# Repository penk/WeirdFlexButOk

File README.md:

## WeirdFlexButOk 

A hot-swappable unibody ergo split keyboard.

This is inspired by Joe Scotto's handwired [ScottoErgo](https://scottokeebs.com/blogs/keyboards/scottoergo-handwired-keyboard) but opts for Choc spacing and hot-swap sockets, plus a super-bendy 0.8mm PCB with kerf bending cuts. It flexes to follow the case’s contour, providing a 15° tilt and 10° tent from one FR4 PCB. 

## Bill of Materials (BOM)

Quantity | Item 
--- | --- 
1 | RP2040-Zero & Pin headers 
1 | WeirdFlexButOk PCB 
1 | WeirdFlexButOk case & plate
36 | Kailh Choc V1 switches  
36 | Kailh Choc V1 Hot-swap sockets 
36 | 1N4148 diodes (SMD)
2 | WS2812B LEDs (optional, for underglow)
8 | M2x4 heat-set thread inserts
6 | M2x8 standoffs
14 | M2x4 screws 

## Production Files

To place an order for the WeirdFlexButOk PCB:

- Use the Gerber files in the [production/](production/) folder. 
- Optionally, you can utilize the [BOM](production/BOM.csv) and [CPL](production/CPL.csv) files with a PCBA service. All components (except RP2040-Zero) are soldered to the bottom side of the board.

Make sure to select the following specs so the PCB can flex:

- Base Material: `FR4`
- PCB Thickness: `0.8mm` 

The complete PCB design project is in the [kicad/](kicad/) folder. 

## 3D Printable Files 

3D print the case with the provided [STL files](case/). 

|  |  |
|---|---|

There will be a lot of support materials, and the tolerance needs to be tuned right for the switches (14.2x14.2mm) to fit.

I find the following parameters work best for my print:

- Top/Bottom Speed: 30 mm/s 
- Support Structure: Tree
- Fan Speed Override: True
- Support Skin Fan Speed: 100%

## Firmware 

Precompiled VIA-enabled firmware: 

- Flash [penk_weirdflexbutok36_via.uf2](firmware/penk_weirdflexbutok36_via.uf2) to the RP2040-Zero.
- Load the [via.json](firmware/QMK/keyboards/penk/weirdflexbutok36/via.json) file in `Design` tab for [VIA](https://usevia.app) configuration.

## Keycaps

The keycap featured in this image is designed based on the Shiratama profile by [@taneyats](https://twitter.com/taneyats). The original design can be found [here](https://www.taneyats.com/entry/shiratama-profile), and is licensed for non-commercial use under [CC BY-NC 4.0](https://creativecommons.org/licenses/by-nc/4.0).

### Attribution
- **Author:** [@taneyats](https://twitter.com/taneyats)
- **Source:** [Shiratama keycaps](https://taneyats.booth.pm/items/4020198)
- **License:** [Creative Commons Attribution-NonCommercial 4.0 International](https://creativecommons.org/licenses/by-nc/4.0/)

### Derivative Work
The STL file has been modified for Choc spacing and is available here: [Shiratama-choc-1U-set.stl](keycap/Shiratama-choc-1U-set.stl) (Modification by [@penk](https://github.com/penk)).

This adaptation is intended for personal use only.

## Copyright and License
Copyright (c) 2024 Penk Chen. All rights reserved.

All files, except those specifically mentioned as licensed under Creative Commons, are licensed under the MIT license. For more information, see the [LICENSE](LICENSE).

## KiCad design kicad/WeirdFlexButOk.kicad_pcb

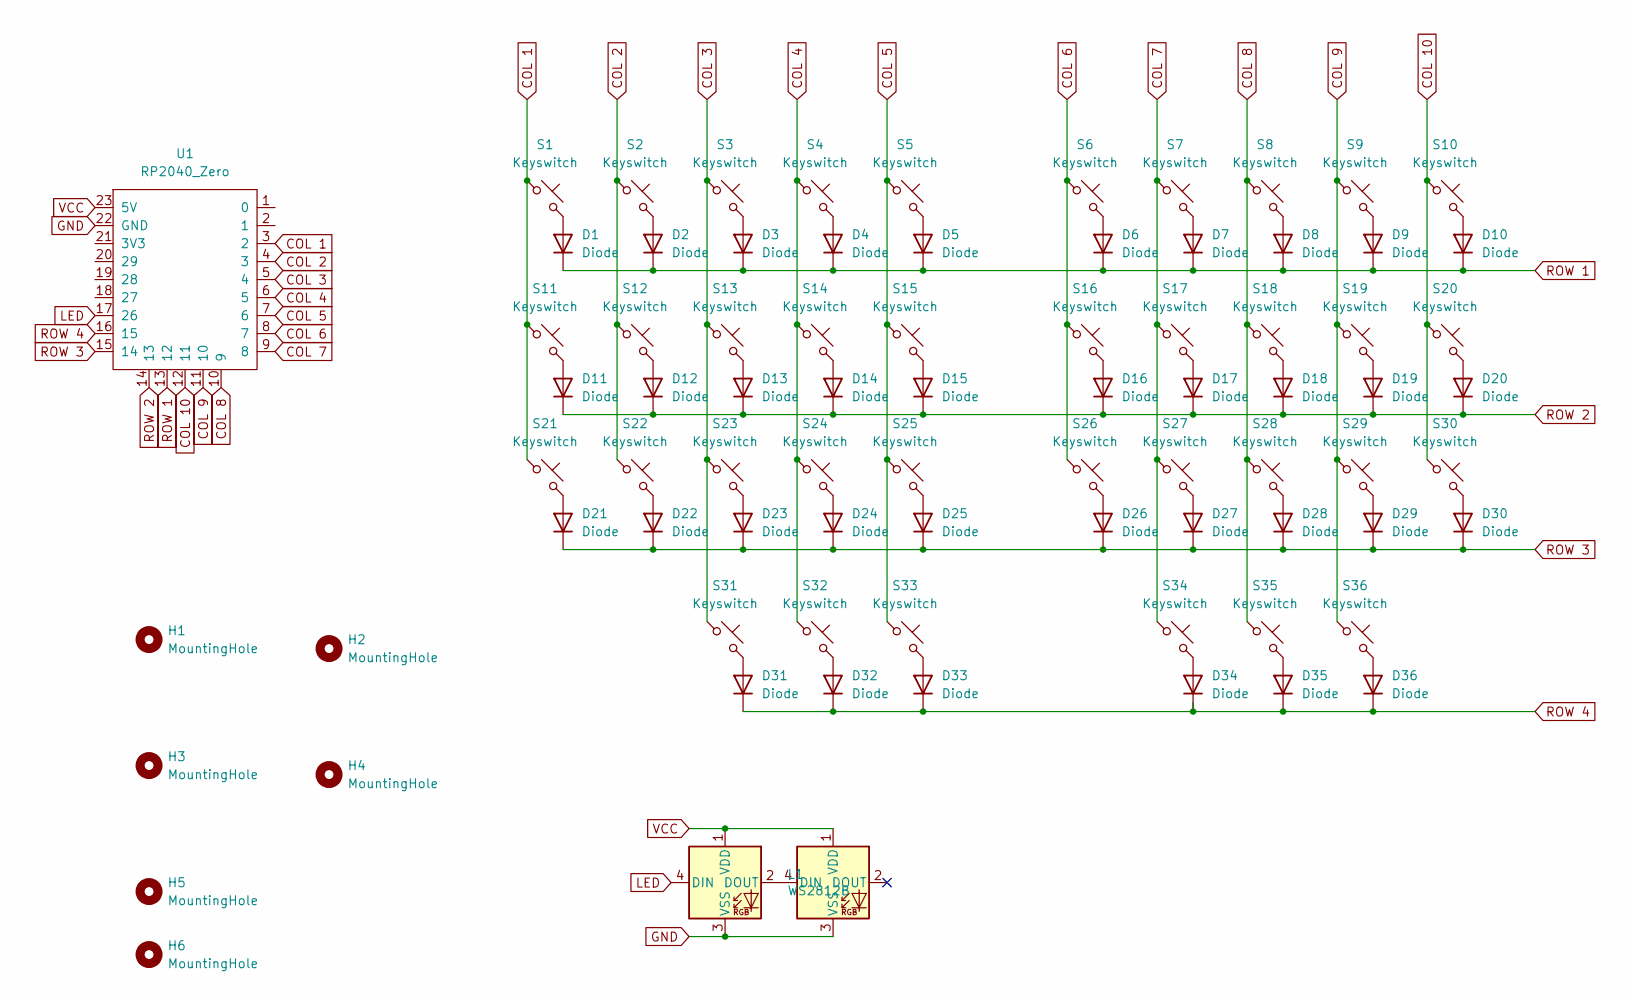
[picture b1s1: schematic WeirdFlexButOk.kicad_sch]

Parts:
D1, D2, D3, D4, D5, D6, D7, D8, D9, D10, D11, D12, D13, D14, D15, D16, D17, D18, D19, D20, D21, D22, D23, D24, D25, D26, D27, D28, D29, D30, D31, D32, D33, D34, D35, D36: Diode; Diode_SOD-123
H1, H2, H3, H4, H5, H6: MountingHole; MountingHole_2.2mm_M2
L1, L2: WS2812B; LED_WS2812B_PLCC4_5.0x5.0mm_P3.2mm
S1, S2, S3, S4, S5, S6, S7, S8, S9, S10, S11, S12, S13, S14, S15, S16, S17, S18, S19, S20, S21, S22, S23, S24, S25, S26, S27, S28, S29, S30, S31, S32, S33, S34, S35, S36: Keyswitch; SW_choc_v1_HS_1u
U1: RP2040_Zero

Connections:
COL 1: S1.1, S11.1, S21.1, U1.3 (2)
COL 2: S2.1, S12.1, S22.1, U1.4 (3)
COL 3: S3.1, S13.1, S23.1, S31.1, U1.5 (4)
COL 4: S4.1, S14.1, S24.1, S32.1, U1.6 (5)
COL 5: S5.1, S15.1, S25.1, S33.1, U1.7 (6)
COL 6: S6.1, S16.1, S26.1, U1.8 (7)
COL 7: S7.1, S17.1, S27.1, S34.1, U1.9 (8)
COL 8: S8.1, S18.1, S28.1, S35.1, U1.10 (9)
COL 9: S9.1, S19.1, S29.1, S36.1, U1.11 (10)
COL 10: S10.1, S20.1, S30.1, U1.12 (11)
GND: L1.3 (VSS), L2.3 (VSS), U1.22 (GND)
LED: L1.4 (DIN), U1.17 (26)
unnamed: D1.2 (A), S1.2
unnamed: D2.2 (A), S2.2
unnamed: D3.2 (A), S3.2
unnamed: D4.2 (A), S4.2
unnamed: D5.2 (A), S5.2
unnamed: D6.2 (A), S6.2
unnamed: D7.2 (A), S7.2
unnamed: D8.2 (A), S8.2
unnamed: D9.2 (A), S9.2
unnamed: D10.2 (A), S10.2
unnamed: D11.2 (A), S11.2
unnamed: D12.2 (A), S12.2
unnamed: D13.2 (A), S13.2
unnamed: D14.2 (A), S14.2
unnamed: D15.2 (A), S15.2
unnamed: D16.2 (A), S16.2
unnamed: D17.2 (A), S17.2
unnamed: D18.2 (A), S18.2
unnamed: D19.2 (A), S19.2
unnamed: D20.2 (A), S20.2
unnamed: D21.2 (A), S21.2
unnamed: D22.2 (A), S22.2
unnamed: D23.2 (A), S23.2
unnamed: D24.2 (A), S24.2
unnamed: D25.2 (A), S25.2
unnamed: D26.2 (A), S26.2
unnamed: D27.2 (A), S27.2
unnamed: D28.2 (A), S28.2
unnamed: D29.2 (A), S29.2
unnamed: D30.2 (A), S30.2
unnamed: D31.2 (A), S31.2
unnamed: D32.2 (A), S32.2
unnamed: D33.2 (A), S33.2
unnamed: D34.2 (A), S34.2
unnamed: D35.2 (A), S35.2
unnamed: D36.2 (A), S36.2
unnamed: L1.2 (DOUT), L2.4 (DIN)
ROW 1: D1.1 (K), D2.1 (K), D3.1 (K), D4.1 (K), D5.1 (K), D6.1 (K), D7.1 (K), D8.1 (K), D9.1 (K), D10.1 (K), U1.13 (12)
ROW 2: D11.1 (K), D12.1 (K), D13.1 (K), D14.1 (K), D15.1 (K), D16.1 (K), D17.1 (K), D18.1 (K), D19.1 (K), D20.1 (K), U1.14 (13)
ROW 3: D21.1 (K), D22.1 (K), D23.1 (K), D24.1 (K), D25.1 (K), D26.1 (K), D27.1 (K), D28.1 (K), D29.1 (K), D30.1 (K), U1.15 (14)
ROW 4: D31.1 (K), D32.1 (K), D33.1 (K), D34.1 (K), D35.1 (K), D36.1 (K), U1.16 (15)
VCC: L1.1 (VDD), L2.1 (VDD), U1.23 (5V)

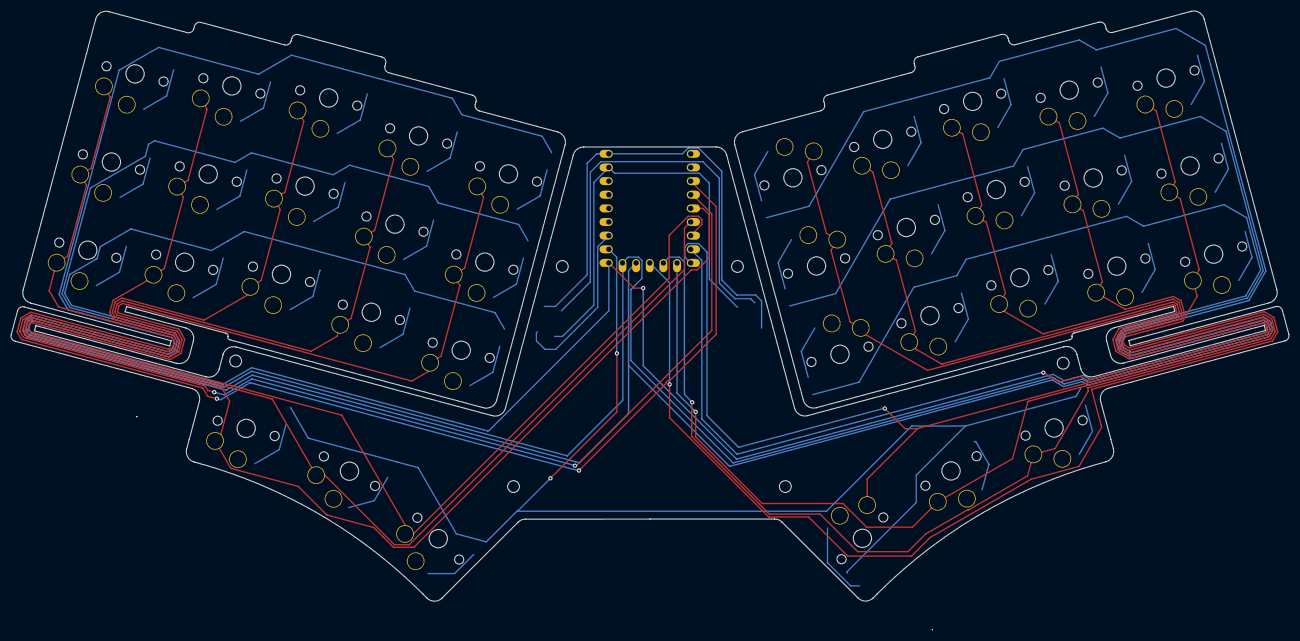
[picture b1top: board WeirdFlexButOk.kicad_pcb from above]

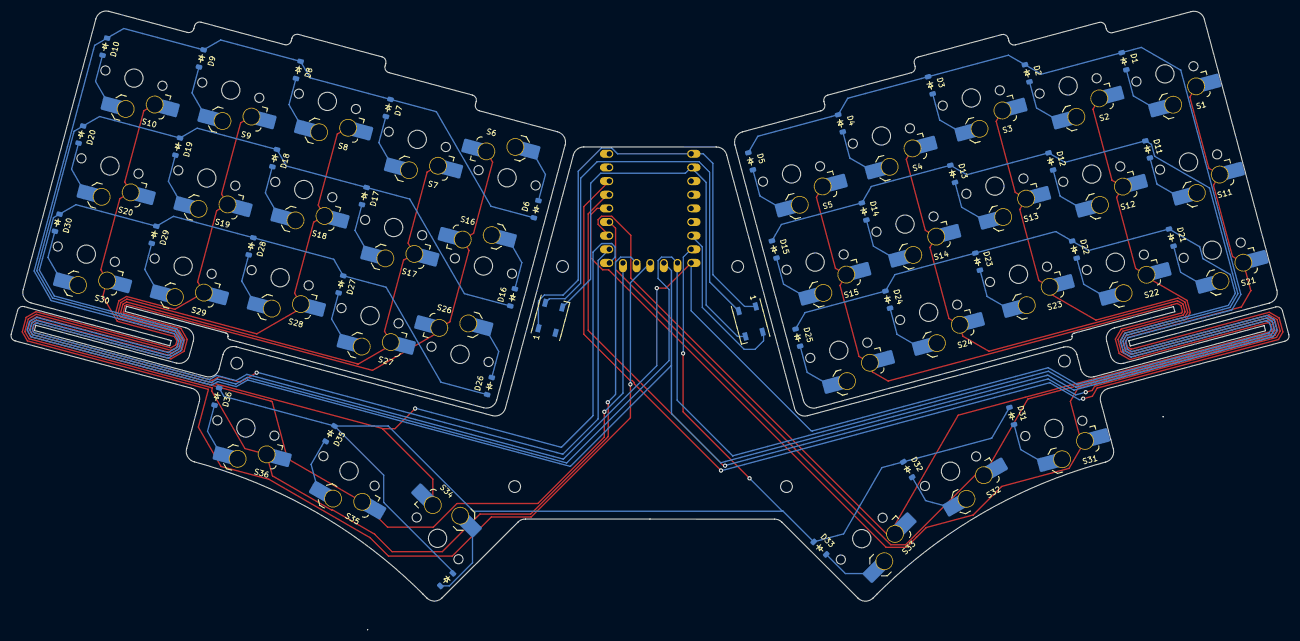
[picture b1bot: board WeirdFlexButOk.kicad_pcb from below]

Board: 2 copper layers, 238.0 x 115.2 mm, 81 parts (74 on the bottom side), 54 nets.

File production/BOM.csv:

Designator,Footprint,Quantity,Value,LCSC Part #
"D1, D10, D11, D12, D13, D14, D15, D16, D17, D18, D19, D2, D20, D21, D22, D23, D24, D25, D26, D27, D28, D29, D3, D30, D31, D32, D33, D34, D35, D36, D4, D5, D6, D7, D8, D9",Diode_SOD-123,36,Diode,C2972760
"L1, L2",LED_WS2812B_PLCC4_5.0x5.0mm_P3.2mm,2,WS2812B,C2761795
"S1, S10, S11, S12, S13, S14, S15, S16, S17, S18, S19, S2, S20, S21, S22, S23, S24, S25, S26, S27, S28, S29, S3, S30, S31, S32, S33, S34, S35, S36, S4, S5, S6, S7, S8, S9",SW_choc_v1_HS_1u,36,Keyswitch,C5333465

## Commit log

2024-06-05 Create LICENSE
2024-06-07 Minor tweaks on the case
2024-06-09 Update firmware to use LED vendor driver
